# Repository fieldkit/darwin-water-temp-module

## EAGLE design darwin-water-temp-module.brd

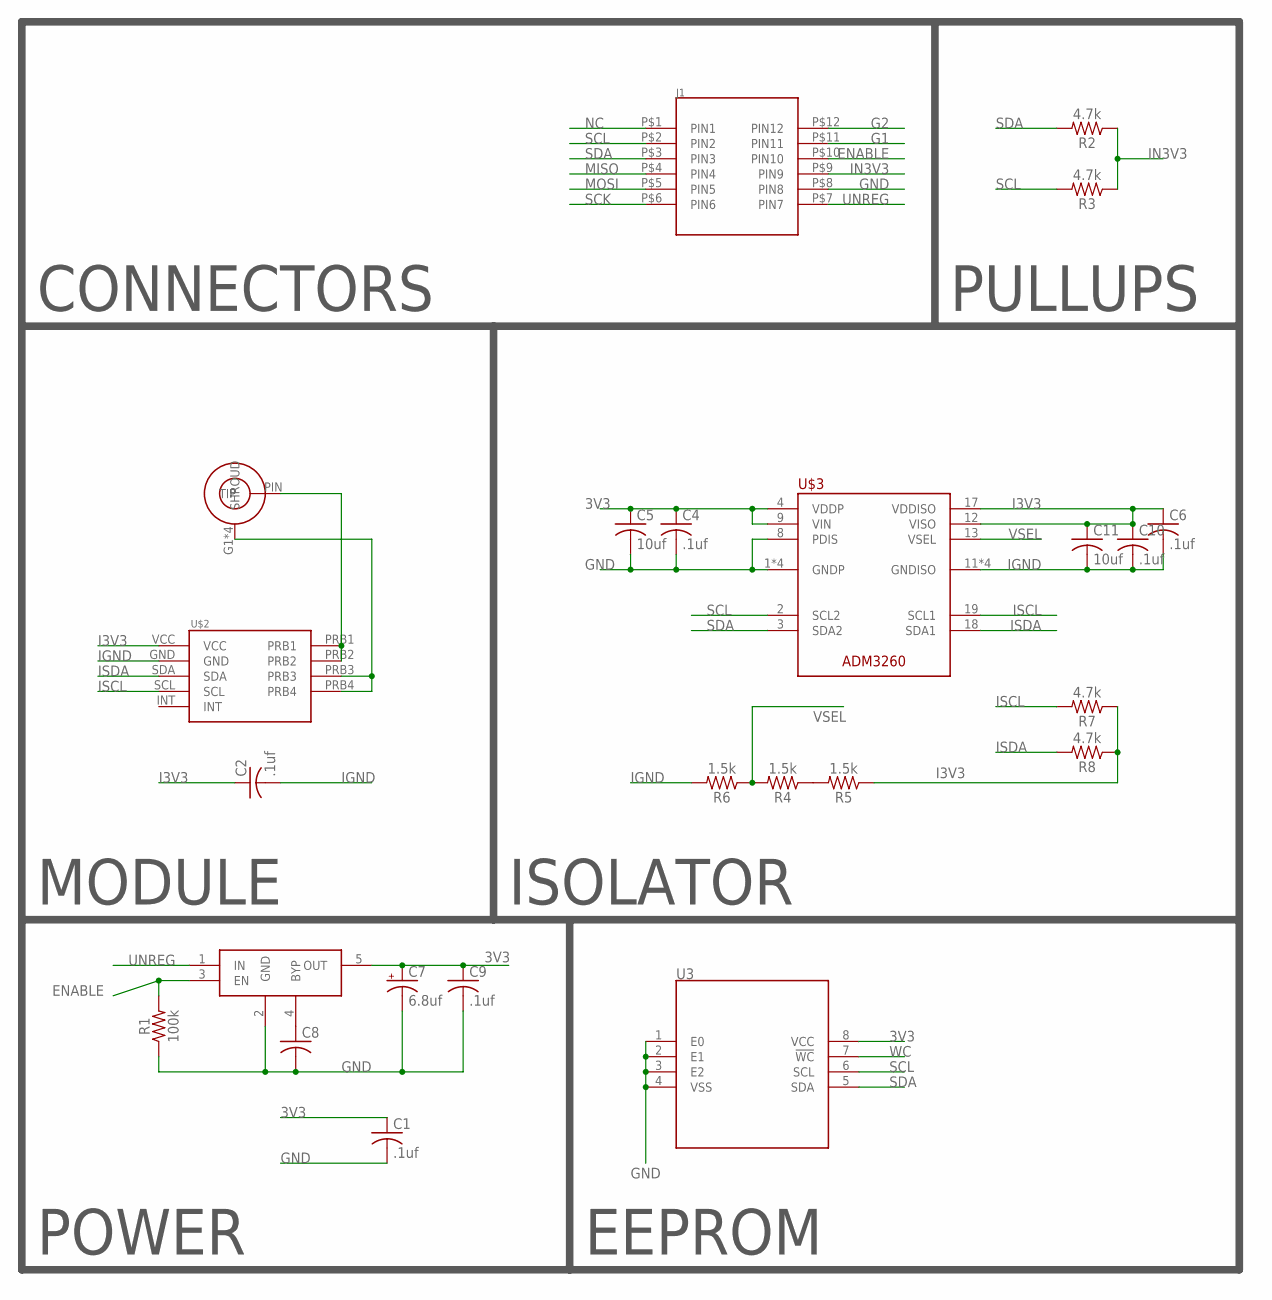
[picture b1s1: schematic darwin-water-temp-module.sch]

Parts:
C1, C2, C4, C6, C9, C10: .1uf; C0603K
C5, C11: 10uf; C0603K
C7: 6.8uf; A/3216-18R
C8: C-USC0603K; C0603K
J1: 2X6-HEADERS; M20-7810645
R1: 100k; 0603
R2, R3, R7, R8: 4.7k; 0603
R4, R5, R6: 1.5k; 0603
U3: M24C02-WMN6TP; SOIC127P600X175-8
U$1: 5-1814832-1
U$2: ATLAS12P; ATLAS-12P
U$3: ADM3260; SOP65P780X200-20
U$4: MIC5219-3.3YM5-TR; SOT95P280X145-5

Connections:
3V3: C1.1, C4.1, C5.1, C7.+, C9.1, U3.8 (VCC), U$3.4 (VDDP), U$3.9 (VIN), U$4.5 (OUT)
ENABLE: J1.P$10 (PIN10), R1.2, U$4.3 (EN)
G1: J1.P$11 (PIN11)
G2: J1.P$12 (PIN12)
GND: C1.2, C4.2, C5.2, C7.-, C8.2, C9.2, J1.P$8 (PIN8), R1.1, U3.1 (E0), U3.2 (E1), U3.3 (E2), U3.4 (VSS), U$3.1 (GNDP), U$3.5 (GNDP), U$3.7 (GNDP), U$3.8 (PDIS), U$3.10 (GNDP), U$4.2 (GND)
I3V3: C2.1, C6.1, C10.1, C11.1, R5.1, R7.1, R8.1, U$2.VCC, U$3.12 (VISO), U$3.17 (VDDISO)
IGND: C2.2, C6.2, C10.2, C11.2, R6.2, U$2.GND, U$3.11 (GNDISO), U$3.14 (GNDISO), U$3.16 (GNDISO), U$3.20 (GNDISO)
IN3V3: J1.P$9 (PIN9), R2.1, R3.1
ISCL: R7.2, U$2.SCL, U$3.19 (SCL1)
ISDA: R8.2, U$2.SDA, U$3.18 (SDA1)
MISO: J1.P$4 (PIN4)
MOSI: J1.P$5 (PIN5)
unnamed: U$1.PIN (TIP), U$2.PRB1, U$2.PRB2
unnamed: R4.1, R5.2
unnamed: C8.1, U$4.4 (BYP)
NC: J1.P$1 (PIN1)
PG: U$1.G1 (SHROUD), U$1.G2 (SHROUD), U$1.G3 (SHROUD), U$1.G4 (SHROUD), U$2.PRB3, U$2.PRB4
SCK: J1.P$6 (PIN6)
SCL: J1.P$2 (PIN2), R3.2, U3.6 (SCL), U$3.2 (SCL2)
SDA: J1.P$3 (PIN3), R2.2, U3.5 (SDA), U$3.3 (SDA2)
UNREG: J1.P$7 (PIN7), U$4.1 (IN)
VSEL: R4.2, R6.1, U$3.13 (VSEL)
WC: U3.7 (!WC)

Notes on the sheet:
CONNECTORS
POWER
EEPROM
PULLUPS
MODULE
ISOLATOR

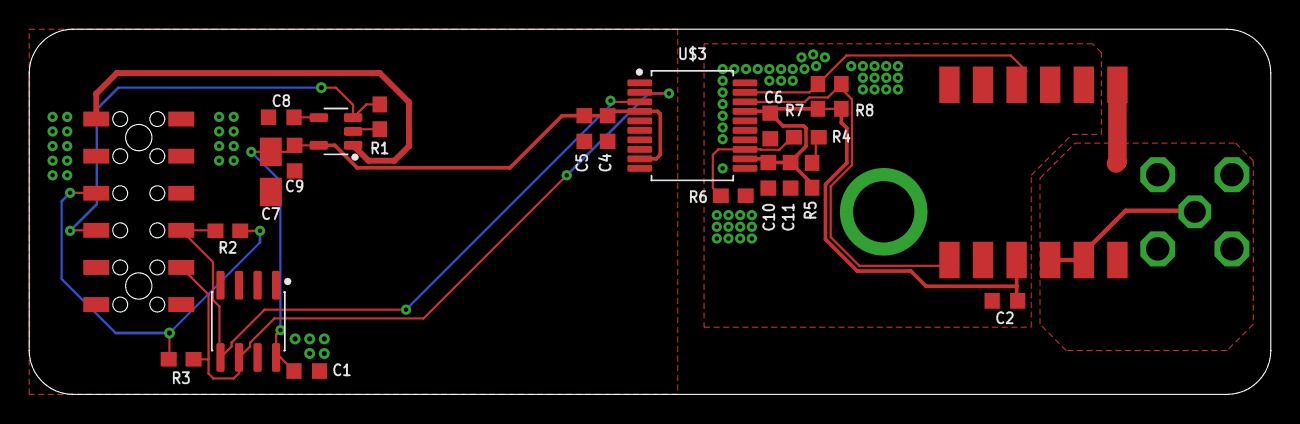
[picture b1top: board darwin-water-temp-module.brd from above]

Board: 2 copper layers, 85.0 x 25.0 mm, 24 parts (0 on the bottom side), 16 nets.

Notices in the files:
parts and their libraries:
SparkFun-Resistors: Licensing: Creative Commons ShareAlike 4.0 International - https://creativecommons.org/licenses/by-sa/4.0
